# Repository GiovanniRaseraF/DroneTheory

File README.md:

# DroneTheory

Teoria e creazione di Flight Controller

Testing di ArduPilot
  - Creazione di un thread a 1Hz di esempio
  - Creazione di un esempio con hal.scheduler->register_timer_process(..)
  - RTOS 
  - DevCall Seguita 2022-08-16

Possibile Erasmus
  - Tetra Drones Ltd
  - Nordic Unmanned AS          - contattata
  - KVS Technologies AS         - contattata
  - https://www.airflight.io/
  - lorenztechnology
  - Everdrone AB
  - UAS Europe AB               - contattata
  - Nordluft Automation

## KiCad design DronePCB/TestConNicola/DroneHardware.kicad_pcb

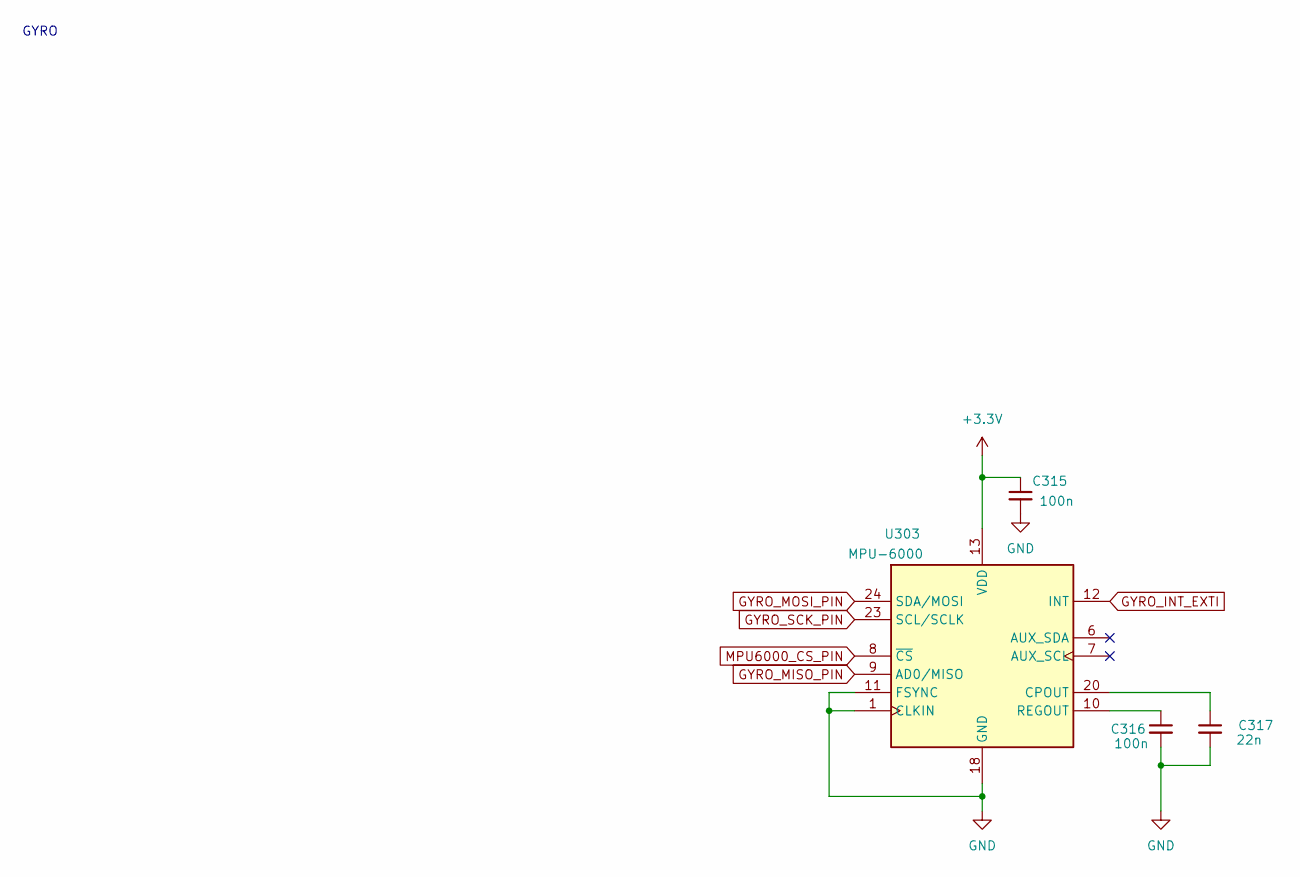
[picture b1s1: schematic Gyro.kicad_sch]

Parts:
C315, C316: 100n; C_0402_1005Metric; LCSC Part # C15195
C317: 22n; C_0402_1005Metric; LCSC Part # C1532
U303: MPU-6000; InvenSense_QFN-24_4x4mm_P0.5mm; LCSC Part # C92401

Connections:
BUCK_VOUT_3V3: C315.1, U303.13 (VDD); also elsewhere on the board
GND: C315.2, C316.2, C317.2, U303.1 (CLKIN), U303.11 (FSYNC), U303.18 (GND); also elsewhere on the board
GYRO_INT_EXTI: U303.12 (INT); also elsewhere on the board
GYRO_MISO_PIN: U303.9 (AD0/MISO); also elsewhere on the board
GYRO_MOSI_PIN: U303.24 (SDA/MOSI); also elsewhere on the board
GYRO_SCK_PIN: U303.23 (SCL/SCLK); also elsewhere on the board
MPU6000_CS_PIN: U303.8 (~CS); also elsewhere on the board
unnamed: C316.1, U303.10 (REGOUT)
unnamed: C317.1, U303.20 (CPOUT)

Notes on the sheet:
GYRO

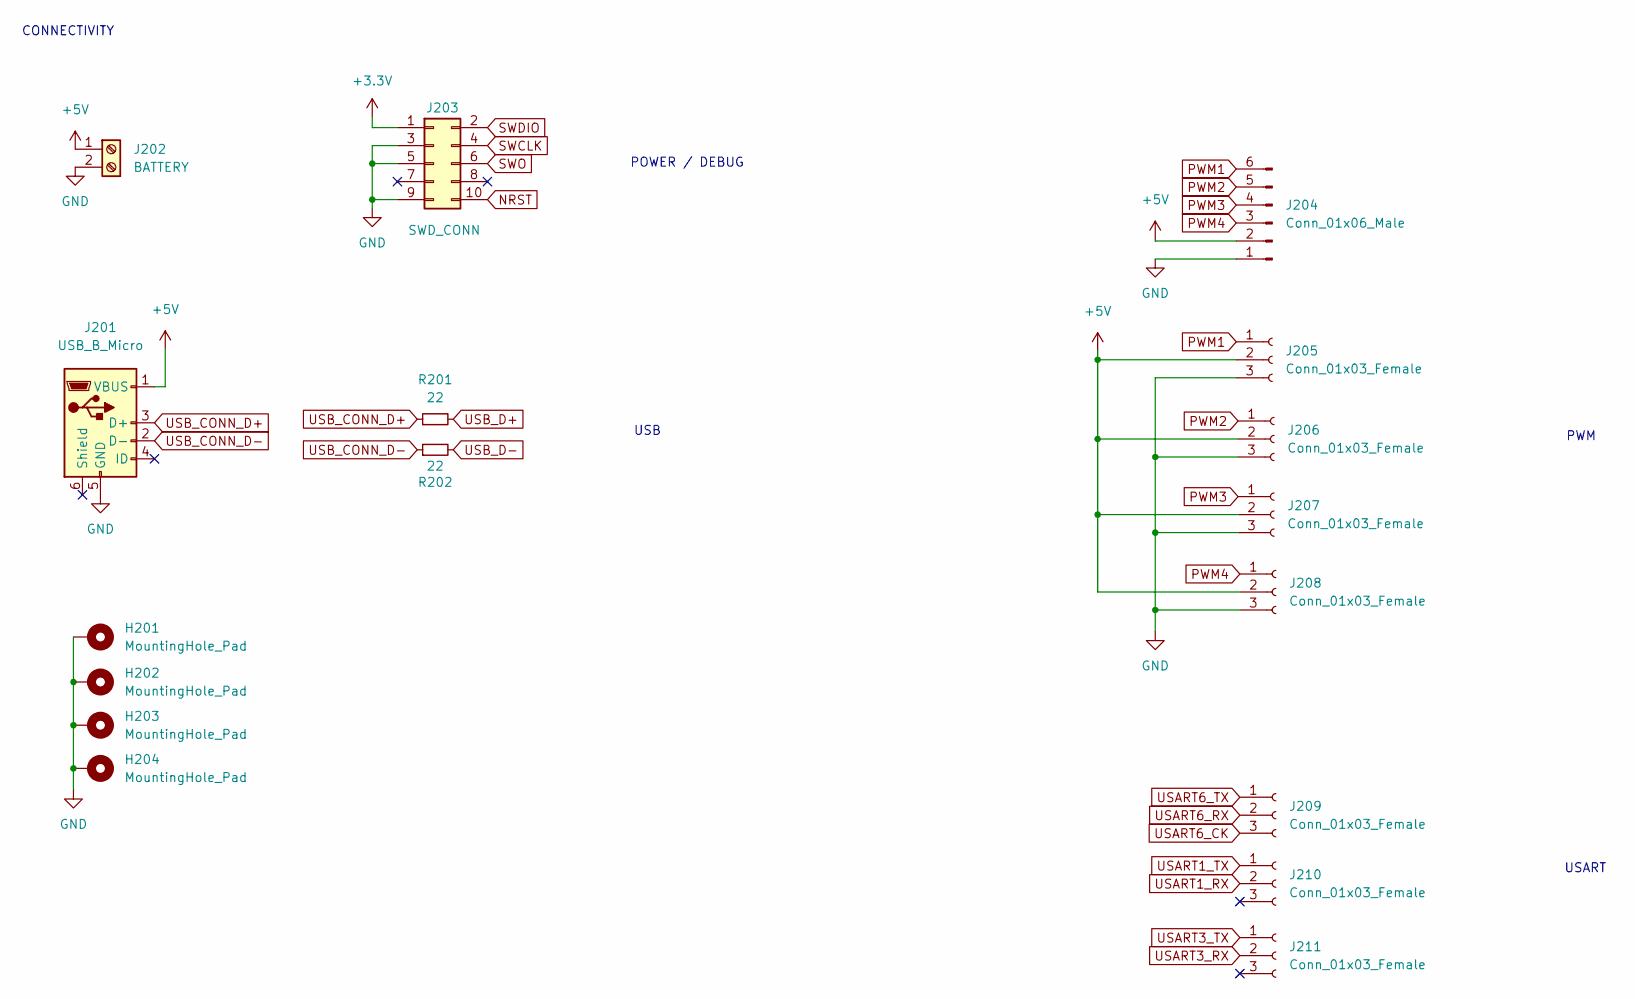
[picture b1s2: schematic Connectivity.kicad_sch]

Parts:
H201, H202, H203, H204: MountingHole_Pad; MountingHole_3.2mm_M3
J201: USB_B_Micro; USB_Micro-B_Molex-105017-0001
J202: BATTERY; PinHeader_1x02_P1.00mm_Vertical
J203: SWD_CONN; PinHeader_2x05_P1.27mm_Vertical_SMD
J204: Conn_01x06_Male; Hirose_DF52-6S-0.8H_1x06-1MP_P0.80mm_Horizontal
J205, J206, J207, J208, J209, J210, J211: Conn_01x03_Female; PinHeader_1x03_P1.00mm_Vertical
R201, R202: 22; R_0402_1005Metric; LCSC Part # C25092

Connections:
+5V: J201.1 (VBUS), J202.1, J204.2, J205.2, J206.2, J207.2, J208.2; also elsewhere on the board
BUCK_VOUT_3V3: J203.1; also elsewhere on the board
GND: H201.1, H202.1, H203.1, H204.1, J201.5 (GND), J202.2, J203.3, J203.5, J203.9, J204.1, J205.3, J206.3, J207.3, J208.3; also elsewhere on the board
NRST: J203.10; also elsewhere on the board
PWM1: J204.6, J205.1; also elsewhere on the board
PWM2: J204.5, J206.1; also elsewhere on the board
PWM3: J204.4, J207.1; also elsewhere on the board
PWM4: J204.3, J208.1; also elsewhere on the board
SWCLK: J203.4; also elsewhere on the board
SWDIO: J203.2; also elsewhere on the board
SWO: J203.6; also elsewhere on the board
USART1_RX: J210.2; also elsewhere on the board
USART1_TX: J210.1; also elsewhere on the board
USART3_RX: J211.2; also elsewhere on the board
USART3_TX: J211.1; also elsewhere on the board
USART6_CK: J209.3; also elsewhere on the board
USART6_RX: J209.2; also elsewhere on the board
USART6_TX: J209.1; also elsewhere on the board
USB_CONN_D+: J201.3 (D+), R201.1
USB_CONN_D-: J201.2 (D-), R202.1
USB_D+: R201.2; also elsewhere on the board
USB_D-: R202.2; also elsewhere on the board

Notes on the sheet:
POWER / DEBUG
USB
USART
PWM
CONNECTIVITY

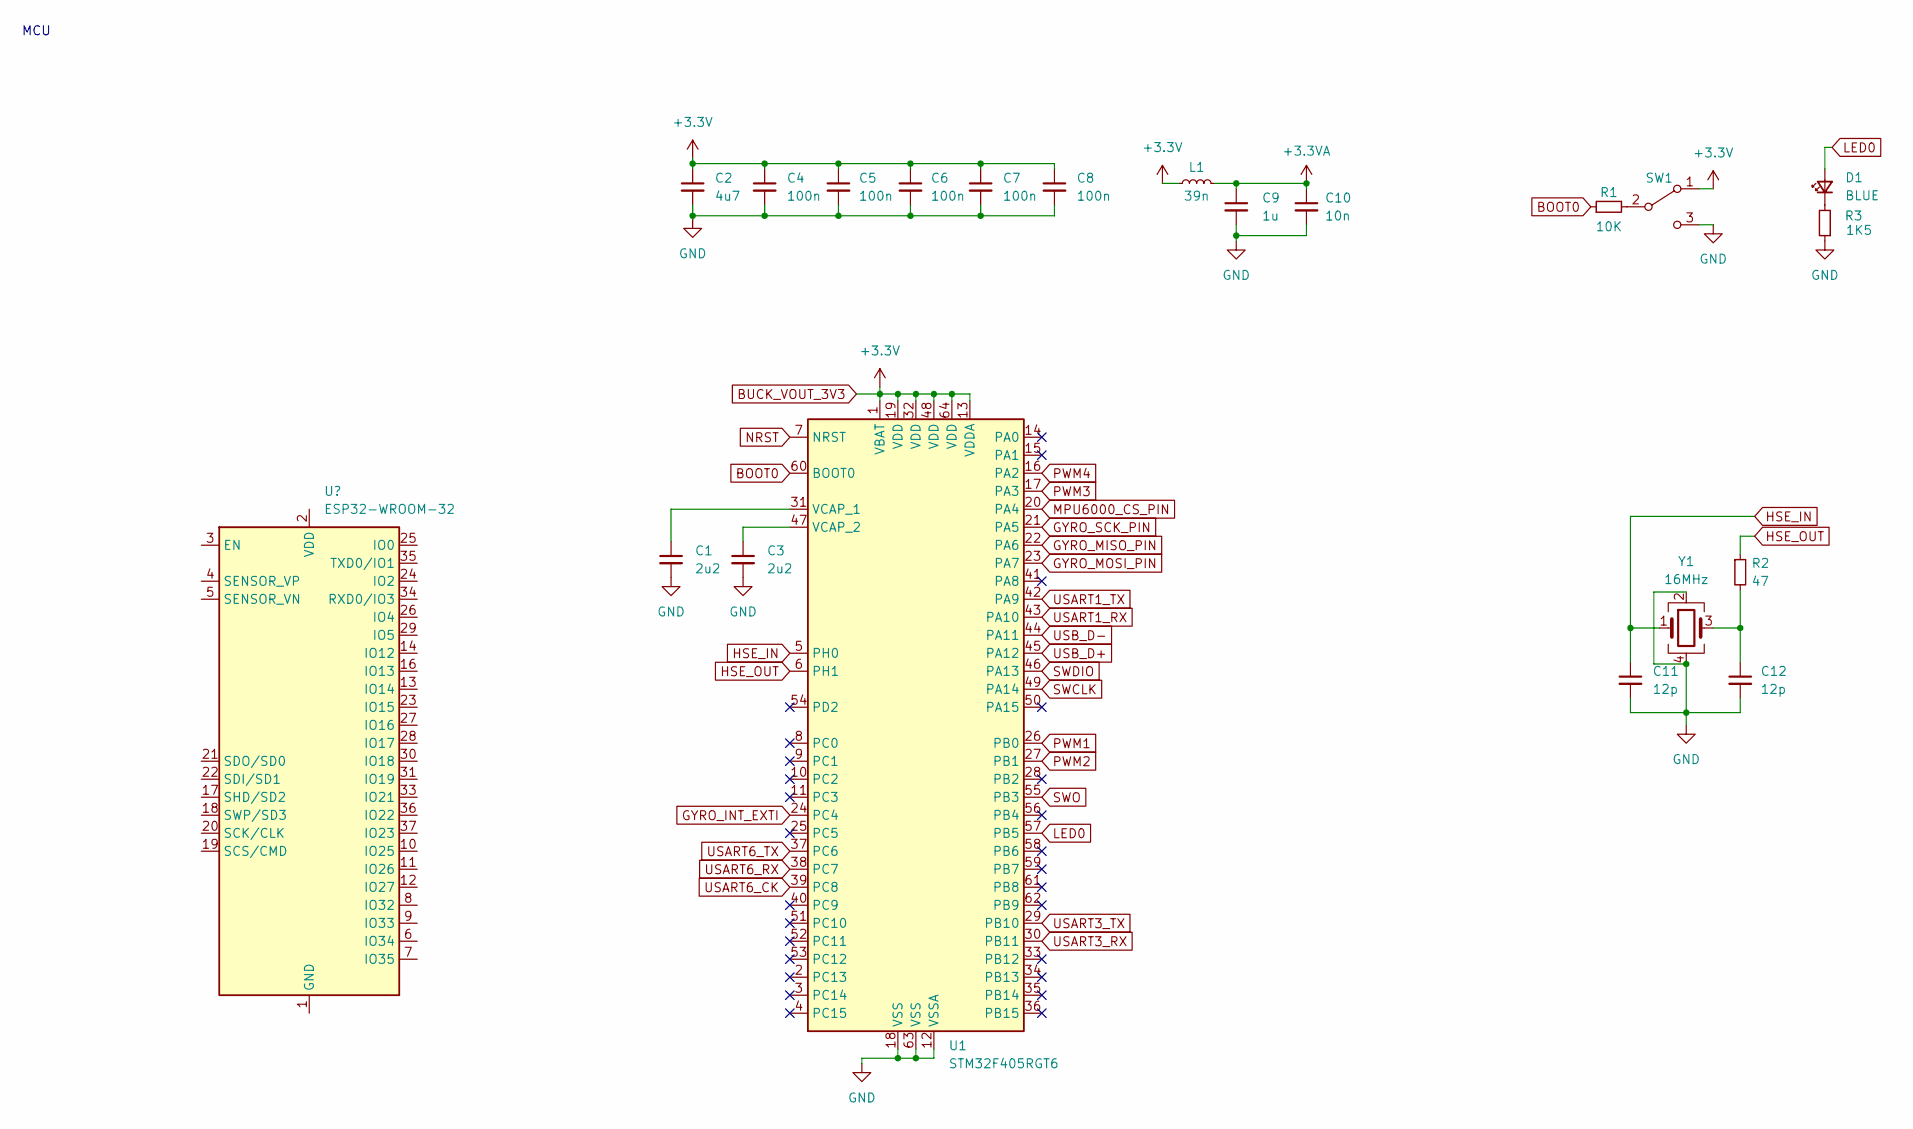
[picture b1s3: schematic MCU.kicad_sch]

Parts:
C1, C3: 2u2; C_0603_1608Metric; LCSC Part # C23630
C2: 4u7; C_0603_1608Metric; LCSC Part # C19666
C4, C5, C6, C7, C8: 100n; C_0402_1005Metric; LCSC Part # C307331
C9: 1u; C_0402_1005Metric; LCSC Part # C52923
C10: 10n; C_0402_1005Metric; LCSC Part # C15195
C11, C12: 12p; C_0402_1005Metric; LCSC Part # C1547
D1: BLUE; LED_0603_1608Metric; LCSC Part # C72041
L1: 39n; L_0402_1005Metric; LCSC Part # C26443
R1: 10K; R_0402_1005Metric; LCSC Part # C25744
R2: 47; R_0402_1005Metric; LCSC Part # C25792
R3: 1K5; R_0603_1608Metric; LCSC Part # C22843
SW1: SW_SPDT; SW_SPST_B3U-1000P
U1: STM32F405RGT6; LQFP-64_10x10mm_P0.5mm; LCSC Part # C15742
Y1: 16MHz; Crystal_SMD_3225-4Pin_3.2x2.5mm; LCSC Part # C13738

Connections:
+3.3VA: C9.1, C10.1, L1.2
BOOT0: R1.1, U1.60 (BOOT0)
BUCK_VOUT_3V3: C2.1, C4.1, C5.1, C6.1, C7.1, C8.1, L1.1, SW1.1 (A), U1.1 (VBAT), U1.13 (VDDA), U1.19 (VDD), U1.32 (VDD), U1.48 (VDD), U1.64 (VDD); also elsewhere on the board
GND: C1.2, C2.2, C3.2, C4.2, C5.2, C6.2, C7.2, C8.2, C9.2, C10.2, C11.2, C12.2, R3.1, SW1.3 (C), U1.12 (VSSA), U1.18 (VSS), U1.63 (VSS), Y1.2, Y1.4; also elsewhere on the board
GYRO_INT_EXTI: U1.24 (PC4); also elsewhere on the board
GYRO_MISO_PIN: U1.22 (PA6); also elsewhere on the board
GYRO_MOSI_PIN: U1.23 (PA7); also elsewhere on the board
GYRO_SCK_PIN: U1.21 (PA5); also elsewhere on the board
HSE_IN: C11.1, U1.5 (PH0), Y1.1
HSE_OUT: R2.1, U1.6 (PH1)
LED0: D1.2 (A), U1.57 (PB5)
MPU6000_CS_PIN: U1.20 (PA4); also elsewhere on the board
NRST: U1.7 (NRST); also elsewhere on the board
unnamed: C1.1, U1.31 (VCAP_1)
unnamed: C3.1, U1.47 (VCAP_2)
unnamed: C12.1, R2.2, Y1.3
unnamed: D1.1 (K), R3.2
unnamed: R1.2, SW1.2 (B)
PWM1: U1.26 (PB0); also elsewhere on the board
PWM2: U1.27 (PB1); also elsewhere on the board
PWM3: U1.17 (PA3); also elsewhere on the board
PWM4: U1.16 (PA2); also elsewhere on the board
SWCLK: U1.49 (PA14); also elsewhere on the board
SWDIO: U1.46 (PA13); also elsewhere on the board
SWO: U1.55 (PB3); also elsewhere on the board
USART1_RX: U1.43 (PA10); also elsewhere on the board
USART1_TX: U1.42 (PA9); also elsewhere on the board
USART3_RX: U1.30 (PB11); also elsewhere on the board
USART3_TX: U1.29 (PB10); also elsewhere on the board
USART6_CK: U1.39 (PC8); also elsewhere on the board
USART6_RX: U1.38 (PC7); also elsewhere on the board
USART6_TX: U1.37 (PC6); also elsewhere on the board
USB_D+: U1.45 (PA12); also elsewhere on the board
USB_D-: U1.44 (PA11); also elsewhere on the board

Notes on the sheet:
MCU

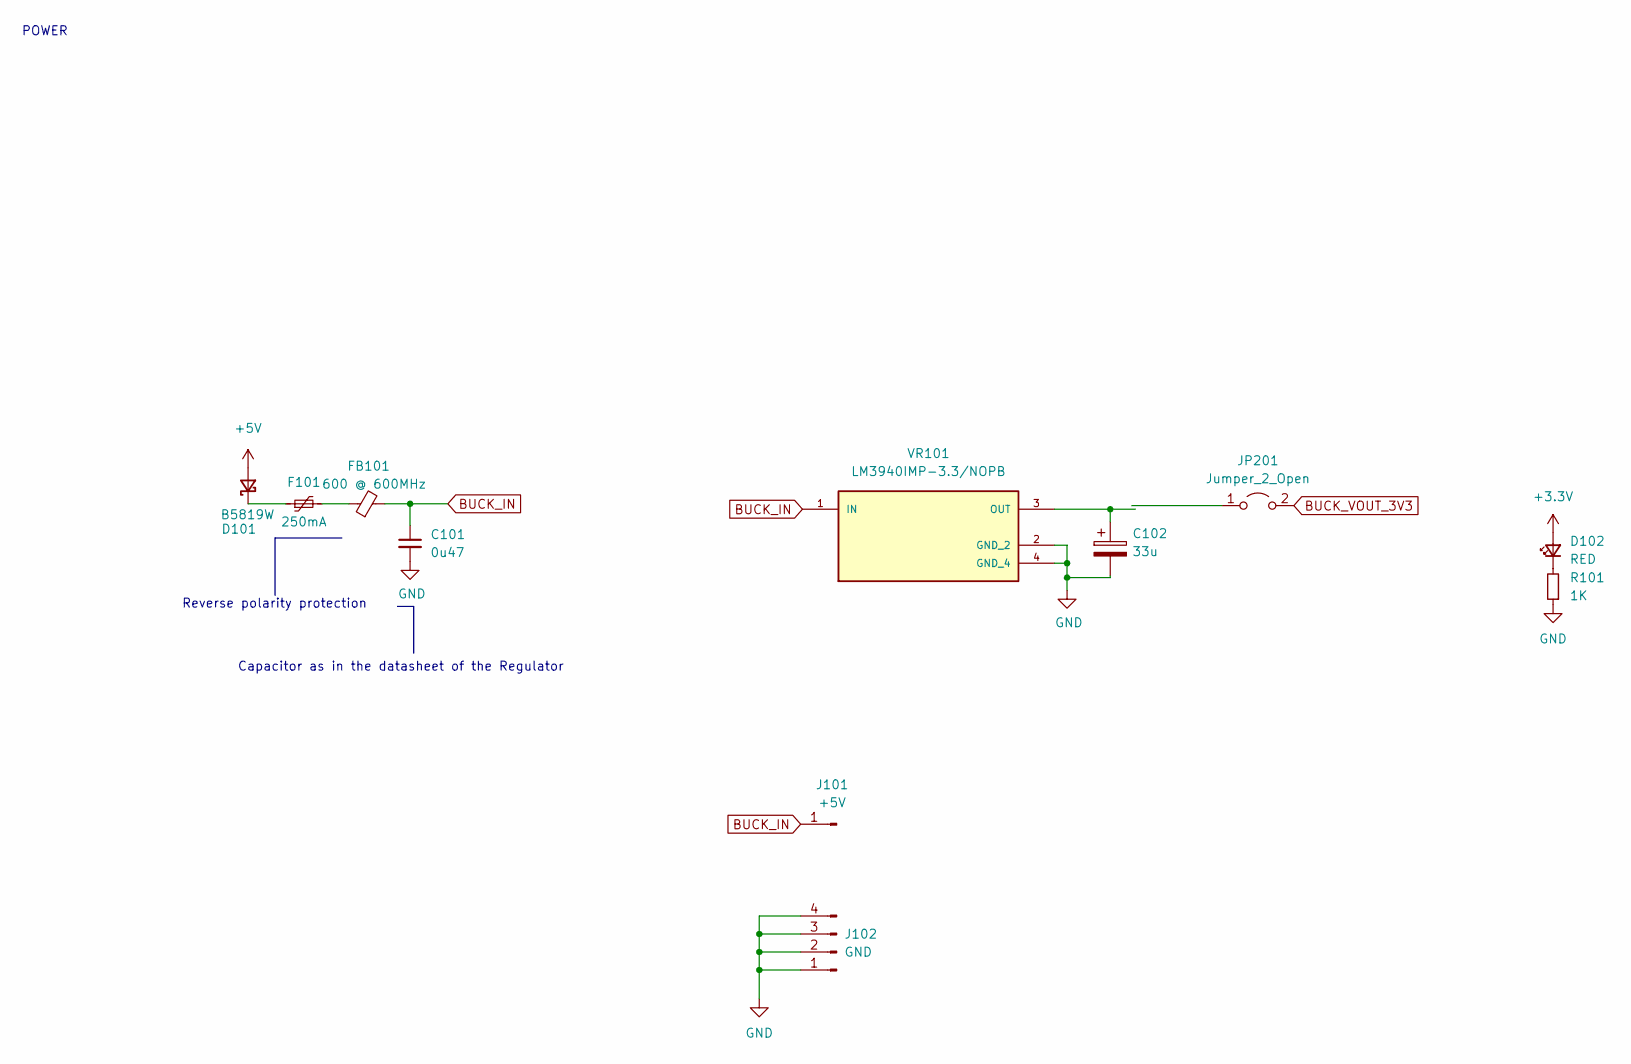
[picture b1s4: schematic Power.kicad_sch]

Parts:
C101: 0u47; C_1206_3216Metric; LCSC Part # C13585
C102: 33u; CP_EIA-1608-08_AVX-J; LCSC Part # C347532
D101: B5819W; D_SOD-123; LCSC Part # C8598
D102: RED; LED_0603_1608Metric; LCSC Part # C2286
F101: 250mA; Fuse_0603_1608Metric; LCSC Part # C151137
FB101: 600 @ 600MHz; L_0805_2012Metric; LCSC Part # C1017
J101: +5V; PinHeader_1x01_P1.00mm_Vertical
J102: GND; PinHeader_1x04_P1.00mm_Vertical
JP201: Jumper_2_Open; SolderJumper-2_P1.3mm_Open_RoundedPad1.0x1.5mm
R101: 1K; R_0603_1608Metric; LCSC Part # C21190
VR101: LM3940IMP-3.3/NOPB; SOT-223; PARTREV G; LCSC Part # C140319

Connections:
+5V: D101.2 (A); also elsewhere on the board
BUCK_IN: C101.1, FB101.2, J101.1, VR101.1 (IN)
BUCK_VOUT_3V3: D102.2 (A), JP201.2 (B); also elsewhere on the board
GND: C101.2, C102.2, J102.1, J102.2, J102.3, J102.4, R101.1, VR101.2 (GND_2), VR101.4 (GND_4); also elsewhere on the board
unnamed: C102.1, VR101.3 (OUT)
unnamed: D101.1 (K), F101.1
unnamed: D102.1 (K), R101.2
unnamed: F101.2, FB101.1

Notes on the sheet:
Reverse polarity protection
POWER
Capacitor as in the datasheet of the Regulator

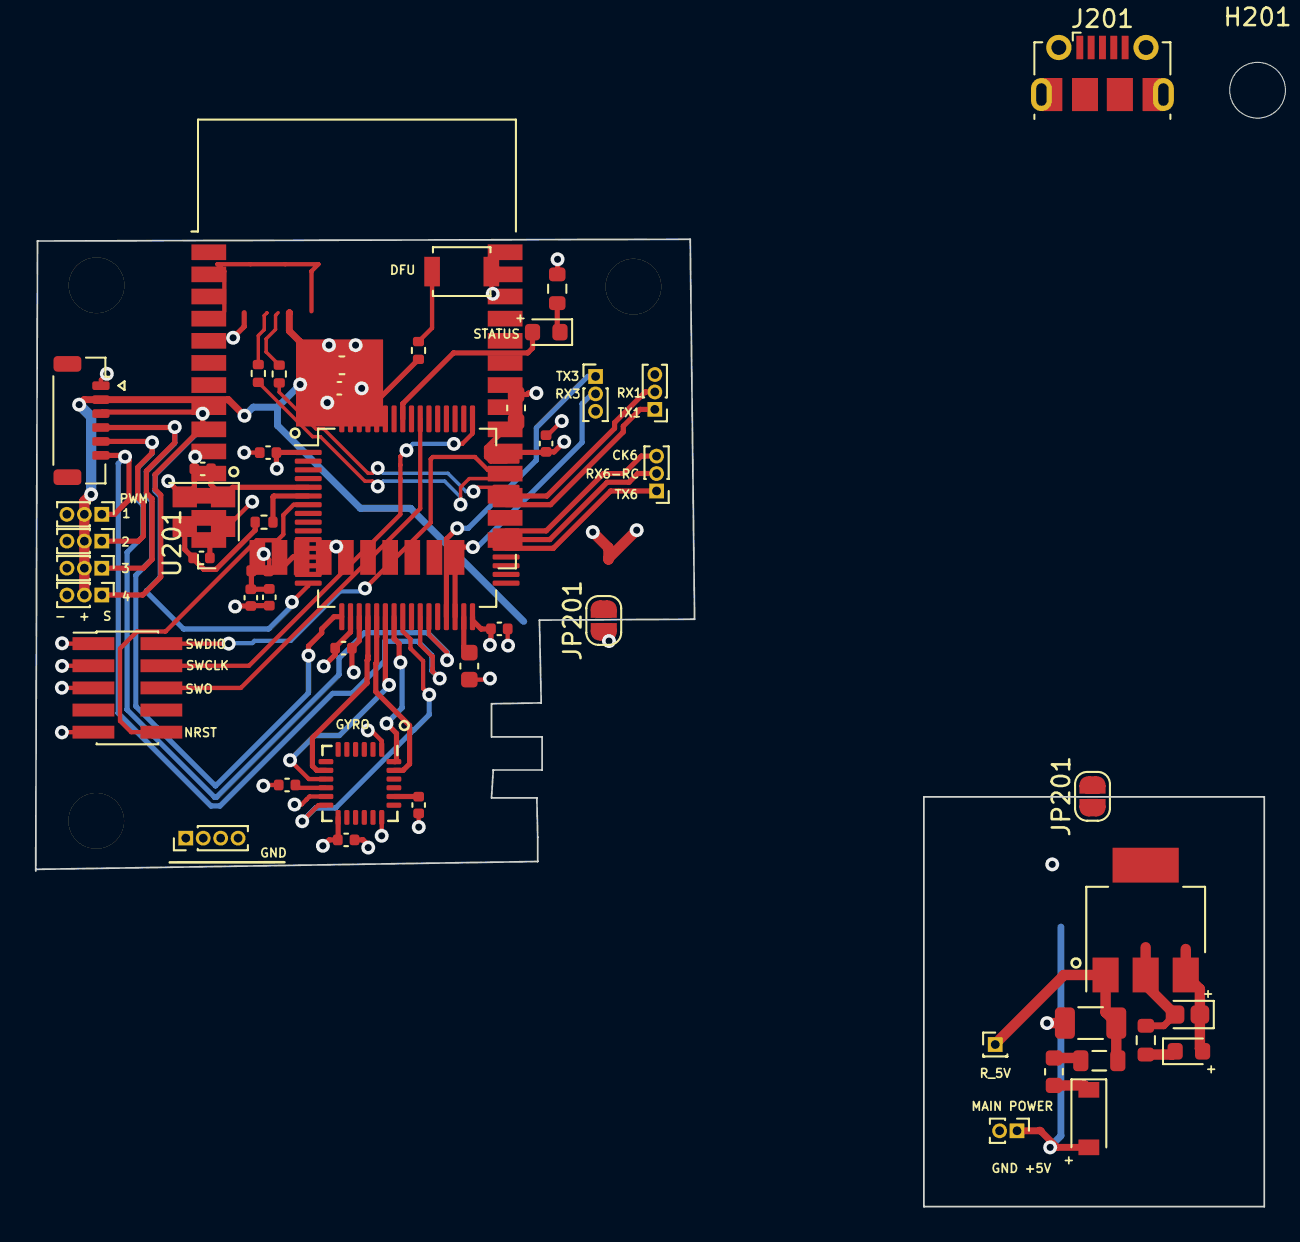
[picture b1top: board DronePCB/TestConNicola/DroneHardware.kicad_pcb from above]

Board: 4 copper layers, 70.5 x 55.5 mm, 54 parts (0 on the bottom side), 45 nets.

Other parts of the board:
JP201#2: Jumper_2_Open; SolderJumper-2_P1.3mm_Open_RoundedPad1.0x1.5mm
U201: ESP32-WROOM-32

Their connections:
unnamed: U201.1 (GND), U201.15 (GND), U201.38 (GND), U201.39 (GND)

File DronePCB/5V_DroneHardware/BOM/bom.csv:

Designator, Comment, Footprint, LCSC
"C101", "0u47", "Capacitor_SMD:C_1206_3216Metric", "C13585"
"C102", "33u", "Capacitor_Tantalum_SMD:CP_EIA-1608-08_AVX-J", "C128344"
"D101", "B5819W", "Diode_SMD:D_SOD-123", "C8598"
"D102", "RED", "LED_SMD:LED_0603_1608Metric", "C2286"
"F101", "250mA", "Fuse:Fuse_0603_1608Metric", "C151137"
"FB101", "600 @ 600MHz", "Inductor_SMD:L_0805_2012Metric", "C1017"
"J101", "+5V", "Connector_PinHeader_1.00mm:PinHeader_1x01_P1.00mm_Vertical", "Power, Start: 100"
"J102", "GND", "Connector_PinHeader_1.00mm:PinHeader_1x04_P1.00mm_Vertical", "Power, Start: 100"
"R101", "1K", "Resistor_SMD:R_0603_1608Metric", "C21190"
"VR101", "LM3940IMP-3.3/NOPB", "Package_TO_SOT_SMD:SOT-223", "Texas Instruments"
"H201", "MountingHole_Pad", "MountingHole:MountingHole_3.2mm_M3", "Connectivity, Start: 200"
"H202", "MountingHole_Pad", "MountingHole:MountingHole_3.2mm_M3", "Connectivity, Start: 200"
"H203", "MountingHole_Pad", "MountingHole:MountingHole_3.2mm_M3", "Connectivity, Start: 200"
"H204", "MountingHole_Pad", "MountingHole:MountingHole_3.2mm_M3", "Connectivity, Start: 200"
"J201", "USB_B_Micro", "Connector_USB:USB_Micro-B_Molex-105017-0001", "Connectivity, Start: 200"
"J202", "BATTERY", "Connector_PinHeader_1.00mm:PinHeader_1x02_P1.00mm_Vertical", "Connectivity, Start: 200"
"J203", "SWD_CONN", "Connector_PinHeader_1.27mm:PinHeader_2x05_P1.27mm_Vertical_SMD", "Connectivity, Start: 200"
"J204", "Conn_01x06_Male", "Connector_Hirose:Hirose_DF52-6S-0.8H_1x06-1MP_P0.80mm_Horizontal", "Connectivity, Start: 200"
"J205", "Conn_01x03_Female", "Connector_PinHeader_1.00mm:PinHeader_1x03_P1.00mm_Vertical", "Connectivity, Start: 200"
"J206", "Conn_01x03_Female", "Connector_PinHeader_1.00mm:PinHeader_1x03_P1.00mm_Vertical", "Connectivity, Start: 200"
"J207", "Conn_01x03_Female", "Connector_PinHeader_1.00mm:PinHeader_1x03_P1.00mm_Vertical", "Connectivity, Start: 200"
"J208", "Conn_01x03_Female", "Connector_PinHeader_1.00mm:PinHeader_1x03_P1.00mm_Vertical", "Connectivity, Start: 200"
"J209", "Conn_01x03_Female", "Connector_PinHeader_1.00mm:PinHeader_1x03_P1.00mm_Vertical", "Connectivity, Start: 200"
"J210", "Conn_01x03_Female", "Connector_PinHeader_1.00mm:PinHeader_1x03_P1.00mm_Vertical", "Connectivity, Start: 200"
"J211", "Conn_01x03_Female", "Connector_PinHeader_1.00mm:PinHeader_1x03_P1.00mm_Vertical", "Connectivity, Start: 200"
"R201", "22", "Resistor_SMD:R_0402_1005Metric", "C25092"
"R202", "22", "Resistor_SMD:R_0402_1005Metric", "C25092"
"C1", "2u2", "Capacitor_SMD:C_0603_1608Metric", "C23630"
"C2", "4u7", "Capacitor_SMD:C_0603_1608Metric", "C19666"
"C3", "2u2", "Capacitor_SMD:C_0603_1608Metric", "C23630"
"C4", "100n", "Capacitor_SMD:C_0402_1005Metric", "C307331"
"C5", "100n", "Capacitor_SMD:C_0402_1005Metric", "C307331"
"C6", "100n", "Capacitor_SMD:C_0402_1005Metric", "C307331"
"C7", "100n", "Capacitor_SMD:C_0402_1005Metric", "C307331"
"C8", "100n", "Capacitor_SMD:C_0402_1005Metric", "C307331"
"C9", "1u", "Capacitor_SMD:C_0402_1005Metric", "C52923"
"C10", "10n", "Capacitor_SMD:C_0402_1005Metric", "C15195"
"C11", "12p", "Capacitor_SMD:C_0402_1005Metric", "C1547"
"C12", "12p", "Capacitor_SMD:C_0402_1005Metric", "C1547"
"D1", "BLUE", "LED_SMD:LED_0603_1608Metric", "C72041"
"L1", "39n", "Inductor_SMD:L_0402_1005Metric", "C26443"
"R1", "10K", "Resistor_SMD:R_0402_1005Metric", "C25744"
"R2", "47", "Resistor_SMD:R_0402_1005Metric", "C25792"
"R3", "1K5", "Resistor_SMD:R_0603_1608Metric", "C22843"
"SW1", "SW_SPDT", "Button_Switch_SMD:SW_SPST_B3U-1000P", "MCU, Start: 0"
"U1", "STM32F405RGT6", "Package_QFP:LQFP-64_10x10mm_P0.5mm", "C15742"
"Y1", "16MHz", "Crystal:Crystal_SMD_3225-4Pin_3.2x2.5mm", "C13738"
"C315", "100n", "Capacitor_SMD:C_0402_1005Metric", "C15195"
"C316", "100n", "Capacitor_SMD:C_0402_1005Metric", "C15195"
"C317", "22n", "Capacitor_SMD:C_0402_1005Metric", "C1532"
"U303", "MPU-6000", "Sensor_Motion:InvenSense_QFN-24_4x4mm_P0.5mm", "C92401"

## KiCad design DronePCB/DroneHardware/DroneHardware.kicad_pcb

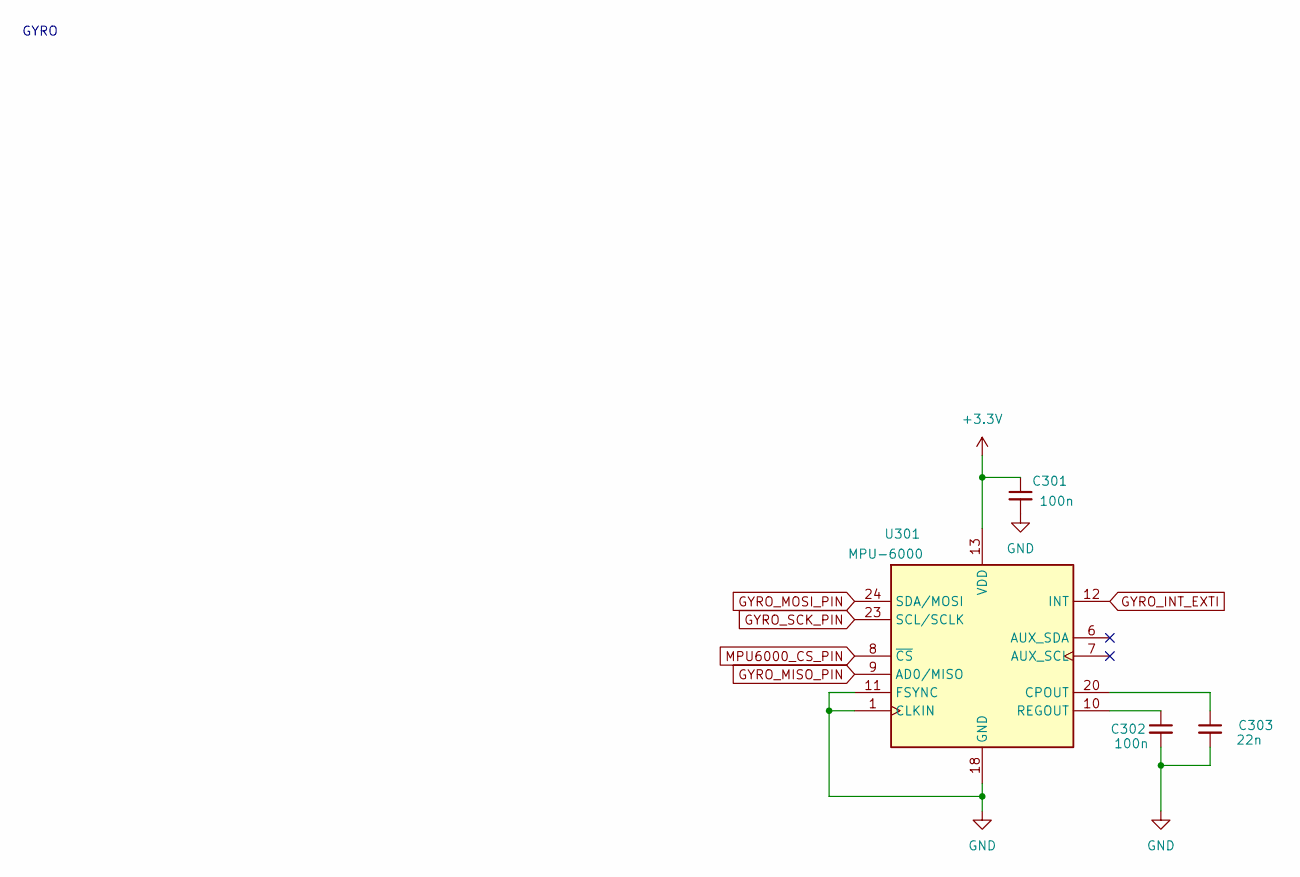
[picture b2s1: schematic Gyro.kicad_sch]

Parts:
C301, C302: 100n; C_0402_1005Metric; LCSC Part # C15195
C303: 22n; C_0402_1005Metric; LCSC Part # C15195
U301: MPU-6000; InvenSense_QFN-24_4x4mm_P0.5mm

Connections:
BUCK_VOUT_3V3: C301.1, U301.13 (VDD); also elsewhere on the board
GND: C301.2, C302.2, C303.2, U301.1 (CLKIN), U301.11 (FSYNC), U301.18 (GND); also elsewhere on the board
GYRO_INT_EXTI: U301.12 (INT); also elsewhere on the board
GYRO_MISO_PIN: U301.9 (AD0/MISO); also elsewhere on the board
GYRO_MOSI_PIN: U301.24 (SDA/MOSI); also elsewhere on the board
GYRO_SCK_PIN: U301.23 (SCL/SCLK); also elsewhere on the board
MPU6000_CS_PIN: U301.8 (~CS); also elsewhere on the board
unnamed: C302.1, U301.10 (REGOUT)
unnamed: C303.1, U301.20 (CPOUT)

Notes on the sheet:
GYRO

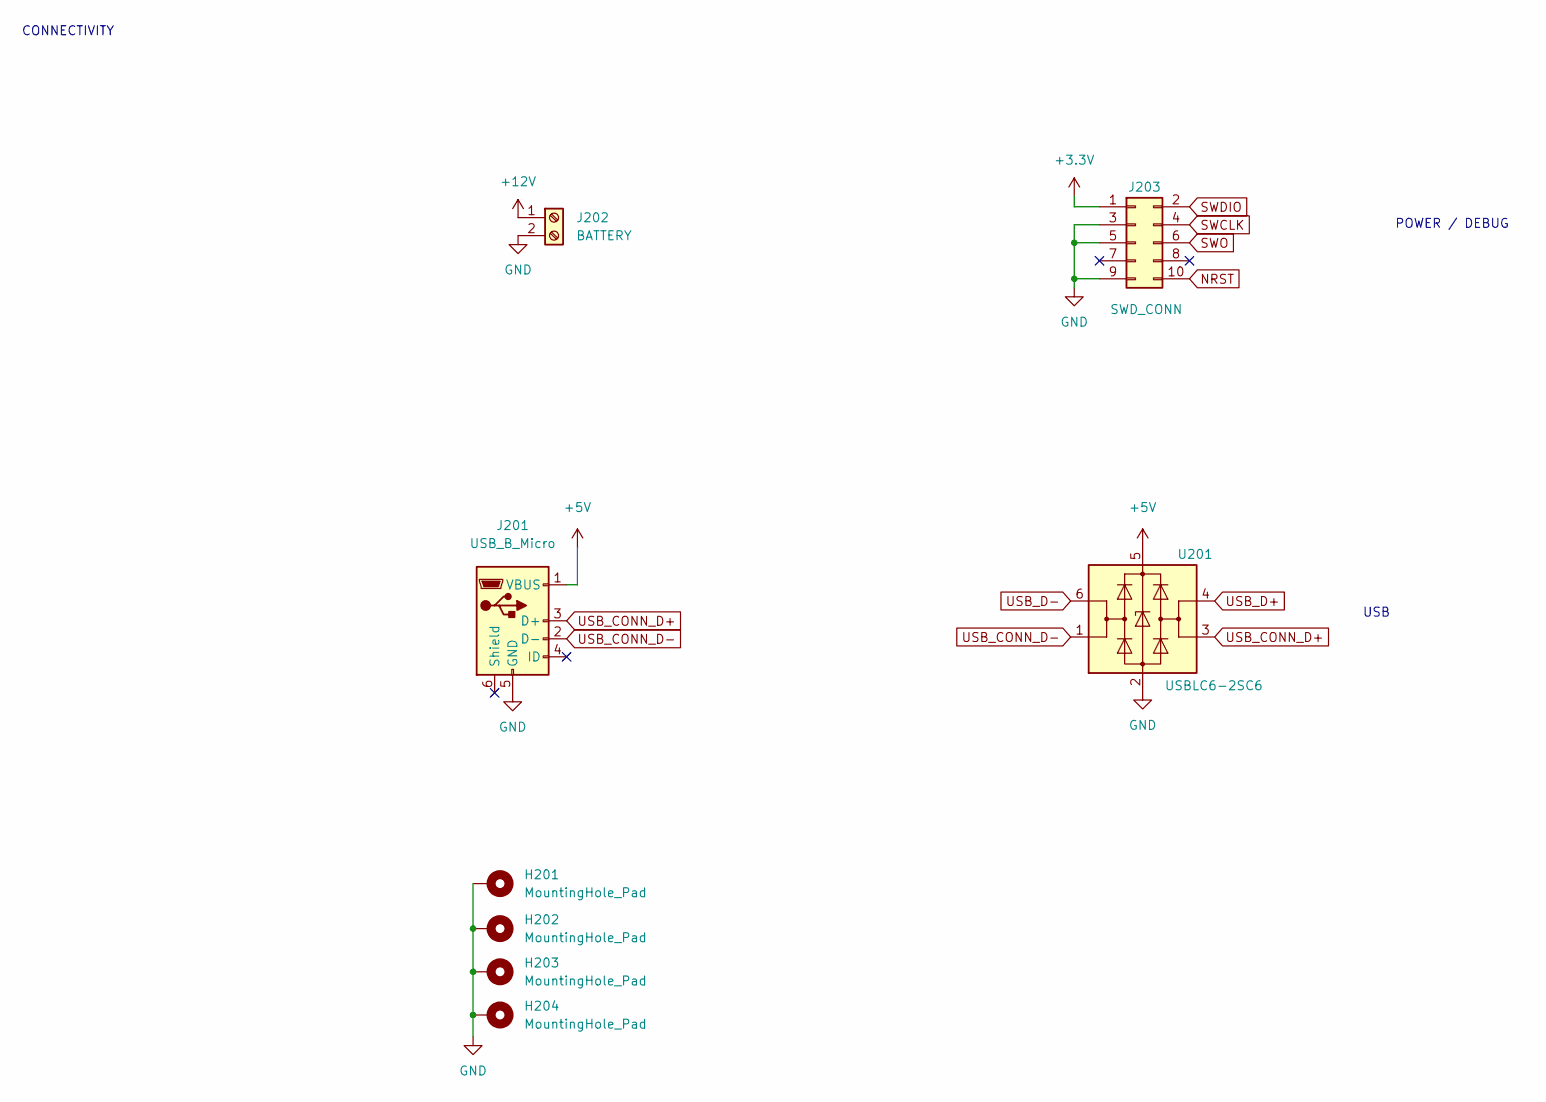
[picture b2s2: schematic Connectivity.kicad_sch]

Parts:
H201, H202, H203, H204: MountingHole_Pad; MountingHole_3.2mm_M3
J201: USB_B_Micro; USB_Micro-B_Molex-105017-0001
J202: BATTERY; PinHeader_1x02_P1.00mm_Vertical
J203: SWD_CONN; PinHeader_2x05_P1.27mm_Vertical_SMD
U201: USBLC6-2SC6; SOT-23-6; LCSC Part # C2827654

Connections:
+5V: J201.1 (VBUS), U201.5 (VBUS); also elsewhere on the board
+12V: J202.1; also elsewhere on the board
BUCK_VOUT_3V3: J203.1; also elsewhere on the board
GND: H201.1, H202.1, H203.1, H204.1, J201.5 (GND), J202.2, J203.3, J203.5, J203.9, U201.2 (GND); also elsewhere on the board
NRST: J203.10; also elsewhere on the board
SWCLK: J203.4; also elsewhere on the board
SWDIO: J203.2; also elsewhere on the board
SWO: J203.6; also elsewhere on the board
USB_CONN_D+: J201.3 (D+), U201.3 (I/O2)
USB_CONN_D-: J201.2 (D-), U201.1 (I/O1)
USB_D+: U201.4 (I/O2); also elsewhere on the board
USB_D-: U201.6 (I/O1); also elsewhere on the board

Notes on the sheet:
POWER / DEBUG
USB
CONNECTIVITY

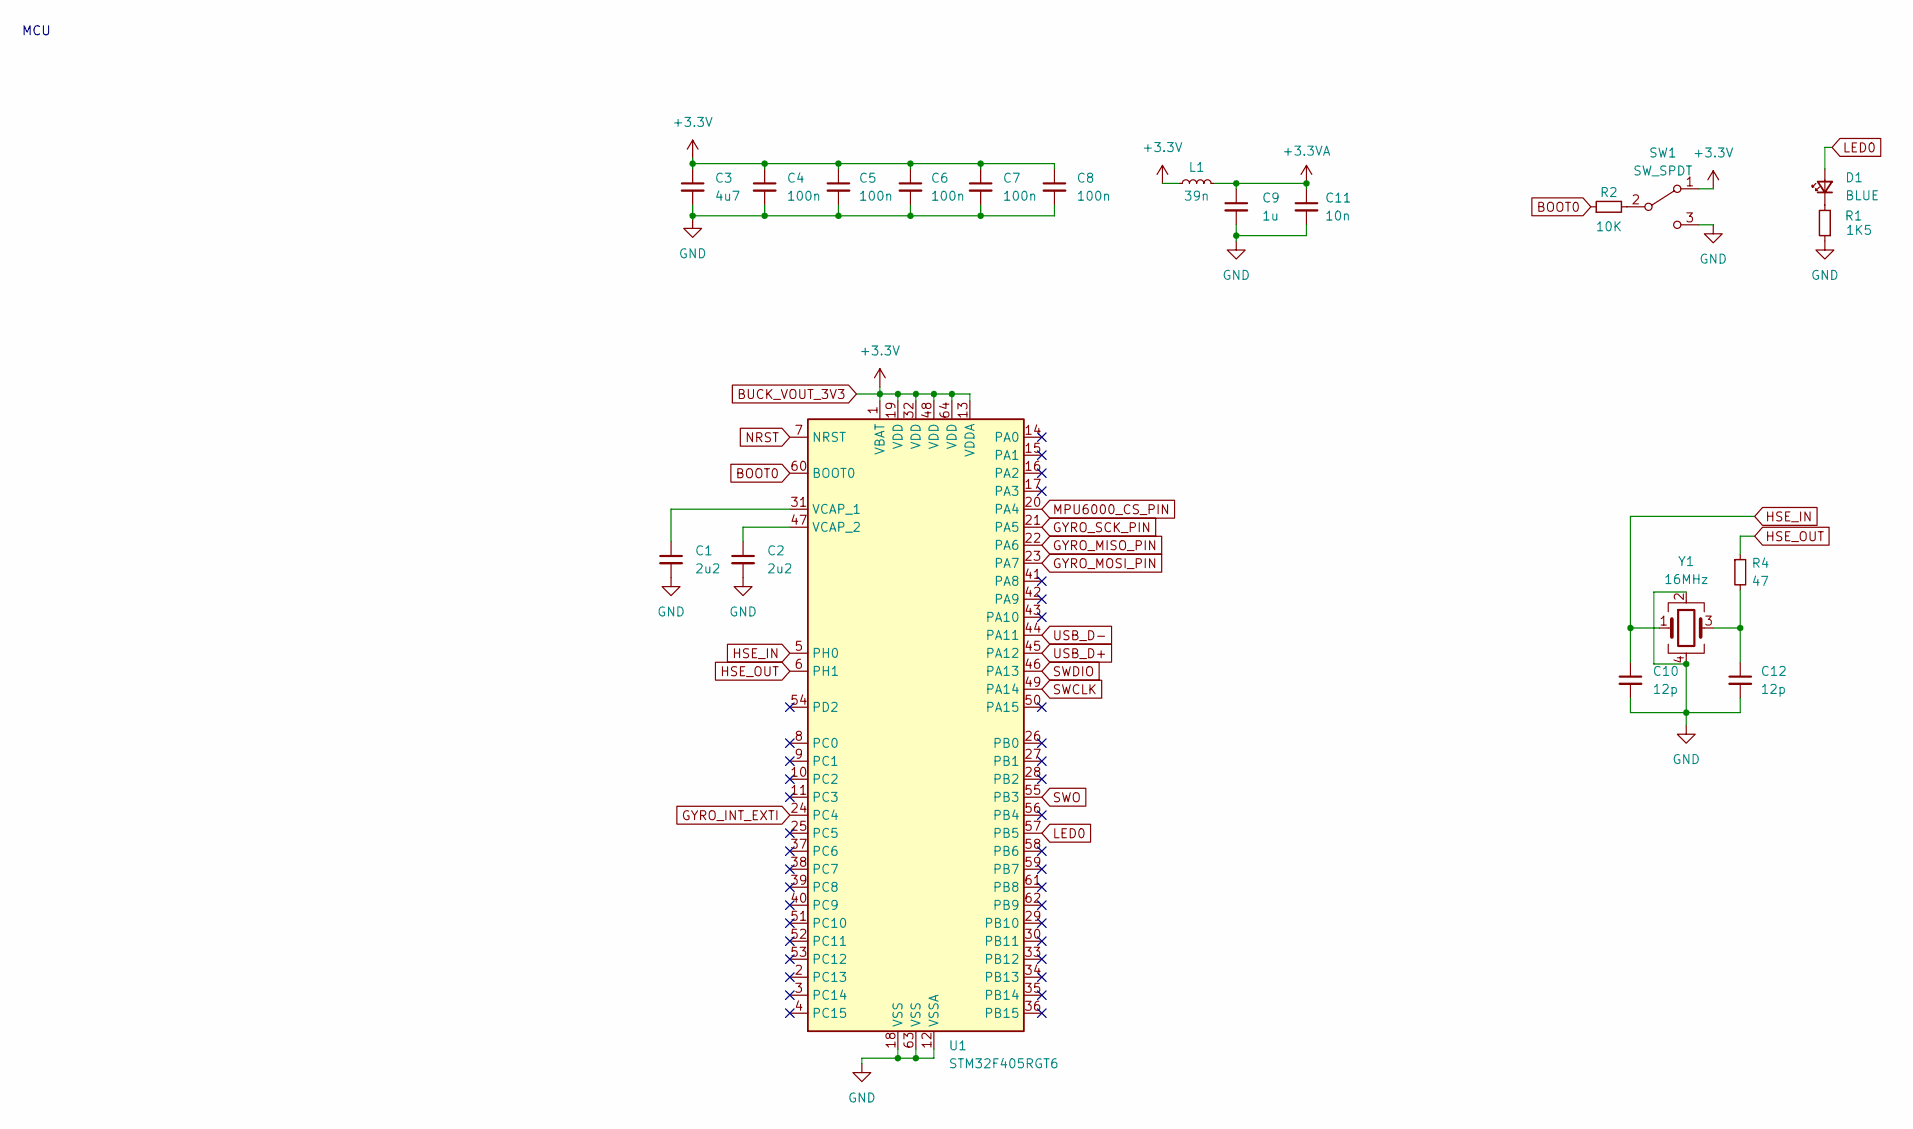
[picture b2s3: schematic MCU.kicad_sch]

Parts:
C1, C2: 2u2; C_0603_1608Metric; LCSC Part # C23630
C3: 4u7; C_0603_1608Metric; LCSC Part # C19666
C4, C5, C6, C7, C8: 100n; C_0402_1005Metric; LCSC Part # C307331
C9: 1u; C_0402_1005Metric; LCSC Part # C52923
C10, C12: 12p; C_0402_1005Metric; LCSC Part # C1547
C11: 10n; C_0402_1005Metric; LCSC Part # C15195
D1: BLUE; LED_0603_1608Metric; LCSC Part # C72041
L1: 39n; L_0402_1005Metric; LCSC Part # C26443
R1: 1K5; R_0603_1608Metric; LCSC Part # C22843
R2: 10K; R_0402_1005Metric; LCSC Part # C25744
R4: 47; R_0402_1005Metric; LCSC Part # C25792
SW1: SW_SPDT; SW_SPDT_PCM12
U1: STM32F405RGT6; LQFP-64_10x10mm_P0.5mm
Y1: 16MHz; Crystal_SMD_3225-4Pin_3.2x2.5mm; LCSC Part # C13738

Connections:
+3.3VA: C9.1, C11.1, L1.2
BOOT0: R2.1, U1.60 (BOOT0)
BUCK_VOUT_3V3: C3.1, C4.1, C5.1, C6.1, C7.1, C8.1, L1.1, SW1.1 (A), U1.1 (VBAT), U1.13 (VDDA), U1.19 (VDD), U1.32 (VDD), U1.48 (VDD), U1.64 (VDD); also elsewhere on the board
GND: C1.2, C2.2, C3.2, C4.2, C5.2, C6.2, C7.2, C8.2, C9.2, C10.2, C11.2, C12.2, R1.1, SW1.3 (C), U1.12 (VSSA), U1.18 (VSS), U1.63 (VSS), Y1.2, Y1.4; also elsewhere on the board
GYRO_INT_EXTI: U1.24 (PC4); also elsewhere on the board
GYRO_MISO_PIN: U1.22 (PA6); also elsewhere on the board
GYRO_MOSI_PIN: U1.23 (PA7); also elsewhere on the board
GYRO_SCK_PIN: U1.21 (PA5); also elsewhere on the board
HSE_IN: C10.1, U1.5 (PH0), Y1.1
HSE_OUT: R4.1, U1.6 (PH1)
LED0: D1.2 (A), U1.57 (PB5)
MPU6000_CS_PIN: U1.20 (PA4); also elsewhere on the board
NRST: U1.7 (NRST); also elsewhere on the board
unnamed: C1.1, U1.31 (VCAP_1)
unnamed: C2.1, U1.47 (VCAP_2)
unnamed: C12.1, R4.2, Y1.3
unnamed: D1.1 (K), R1.2
unnamed: R2.2, SW1.2 (B)
SWCLK: U1.49 (PA14); also elsewhere on the board
SWDIO: U1.46 (PA13); also elsewhere on the board
SWO: U1.55 (PB3); also elsewhere on the board
USB_D+: U1.45 (PA12); also elsewhere on the board
USB_D-: U1.44 (PA11); also elsewhere on the board

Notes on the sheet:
MCU
